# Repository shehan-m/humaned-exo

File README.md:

<p align="center">
  <a>
    
    <h1 align="center">HumanEd Exoskeleton Team</h1>
  </a>
</p>

<p align="center">

  Welcome to the HumanEd Exoskeleton Team Github repository! Check out the [project wiki](https://github.com/shehan-m/humaned-exo/wiki) for more information on the project.
</p>

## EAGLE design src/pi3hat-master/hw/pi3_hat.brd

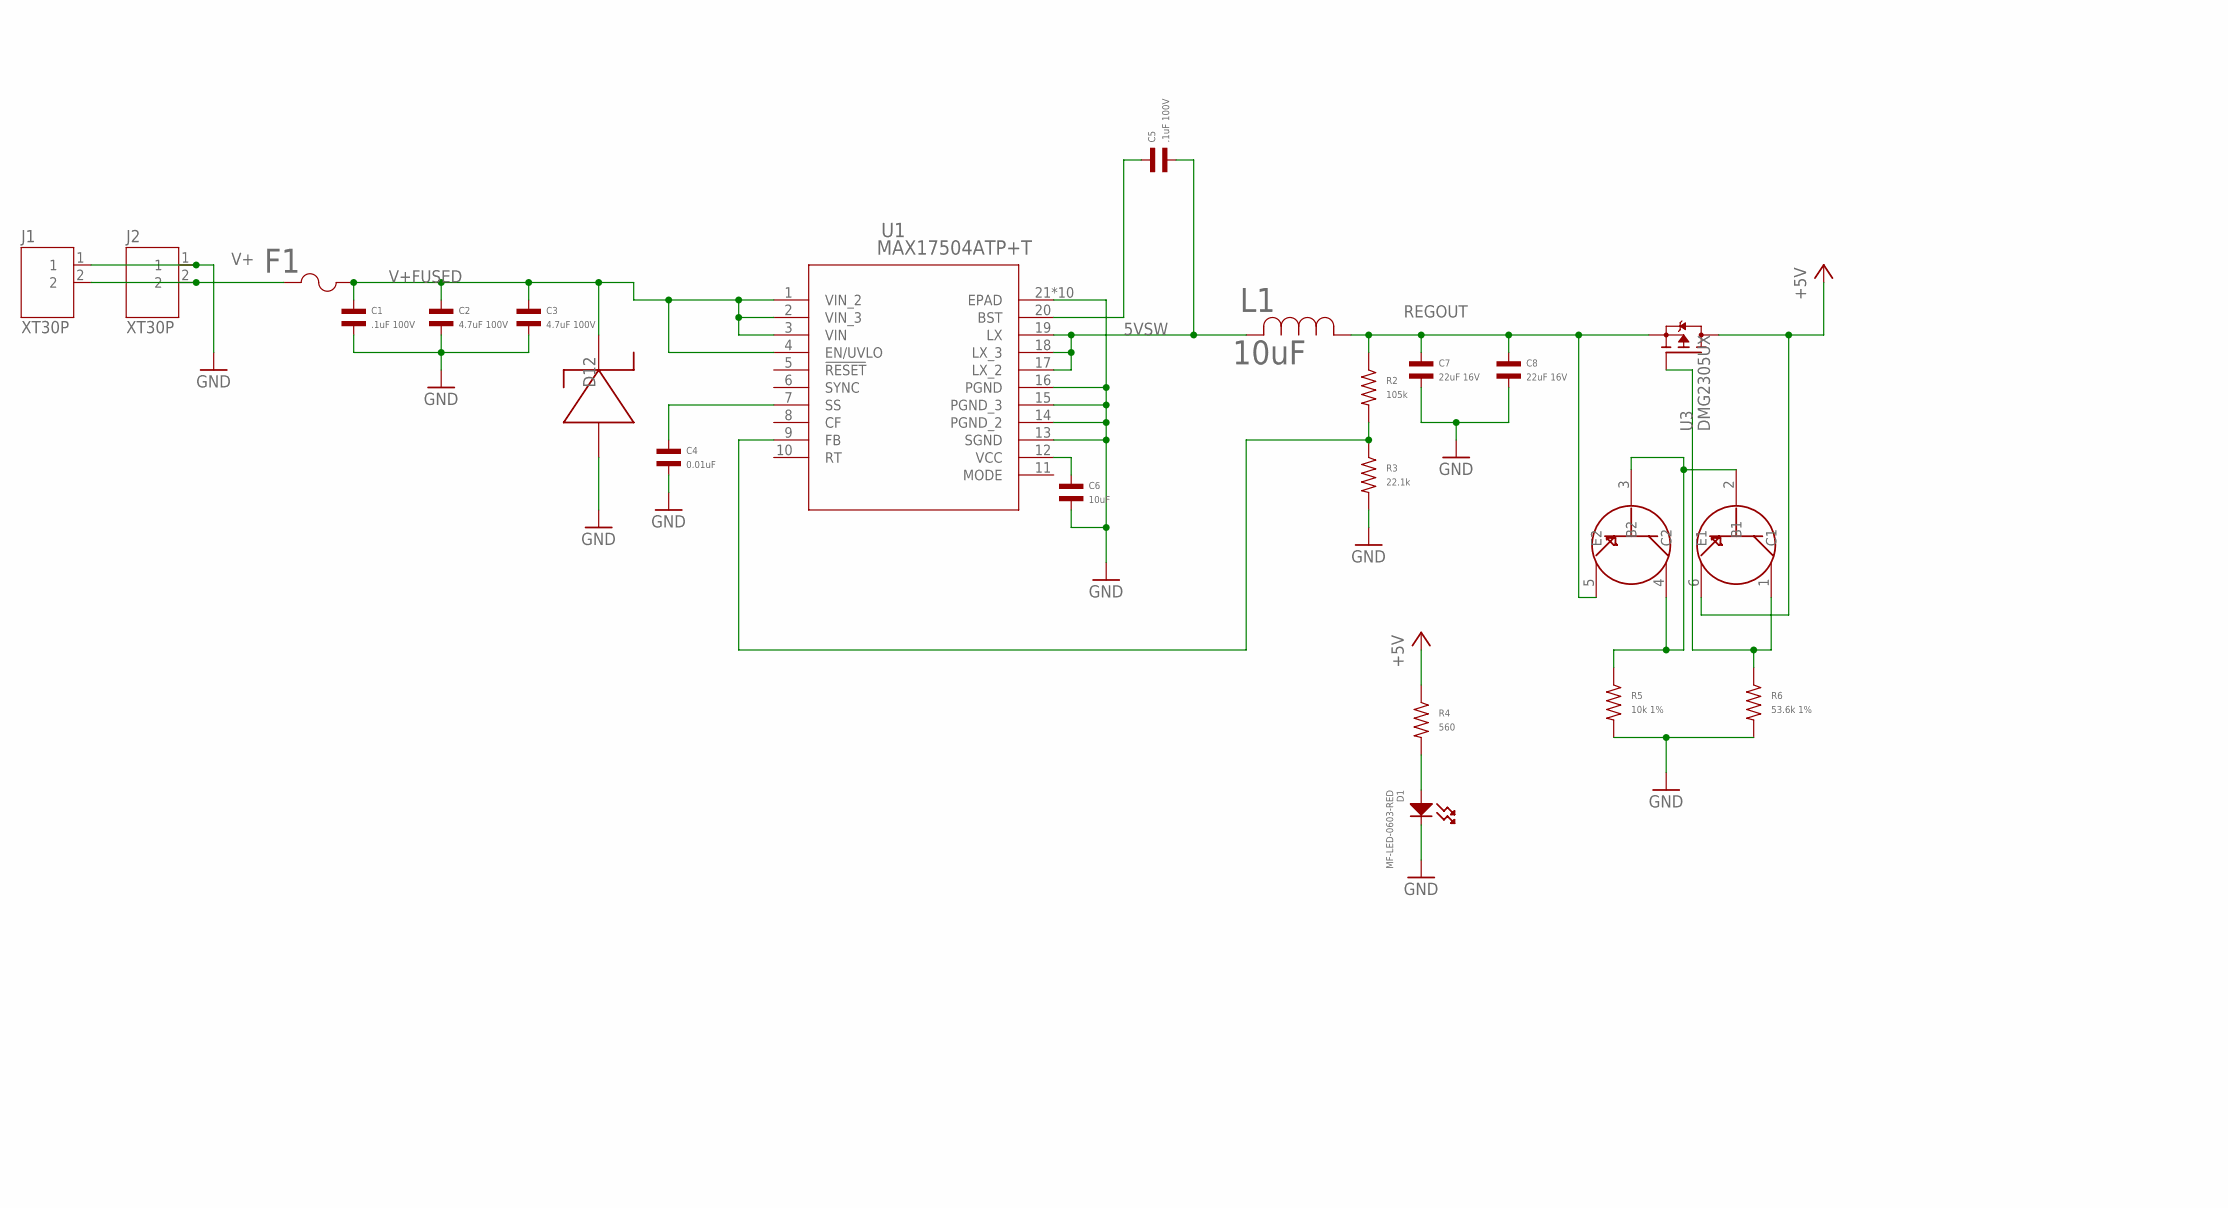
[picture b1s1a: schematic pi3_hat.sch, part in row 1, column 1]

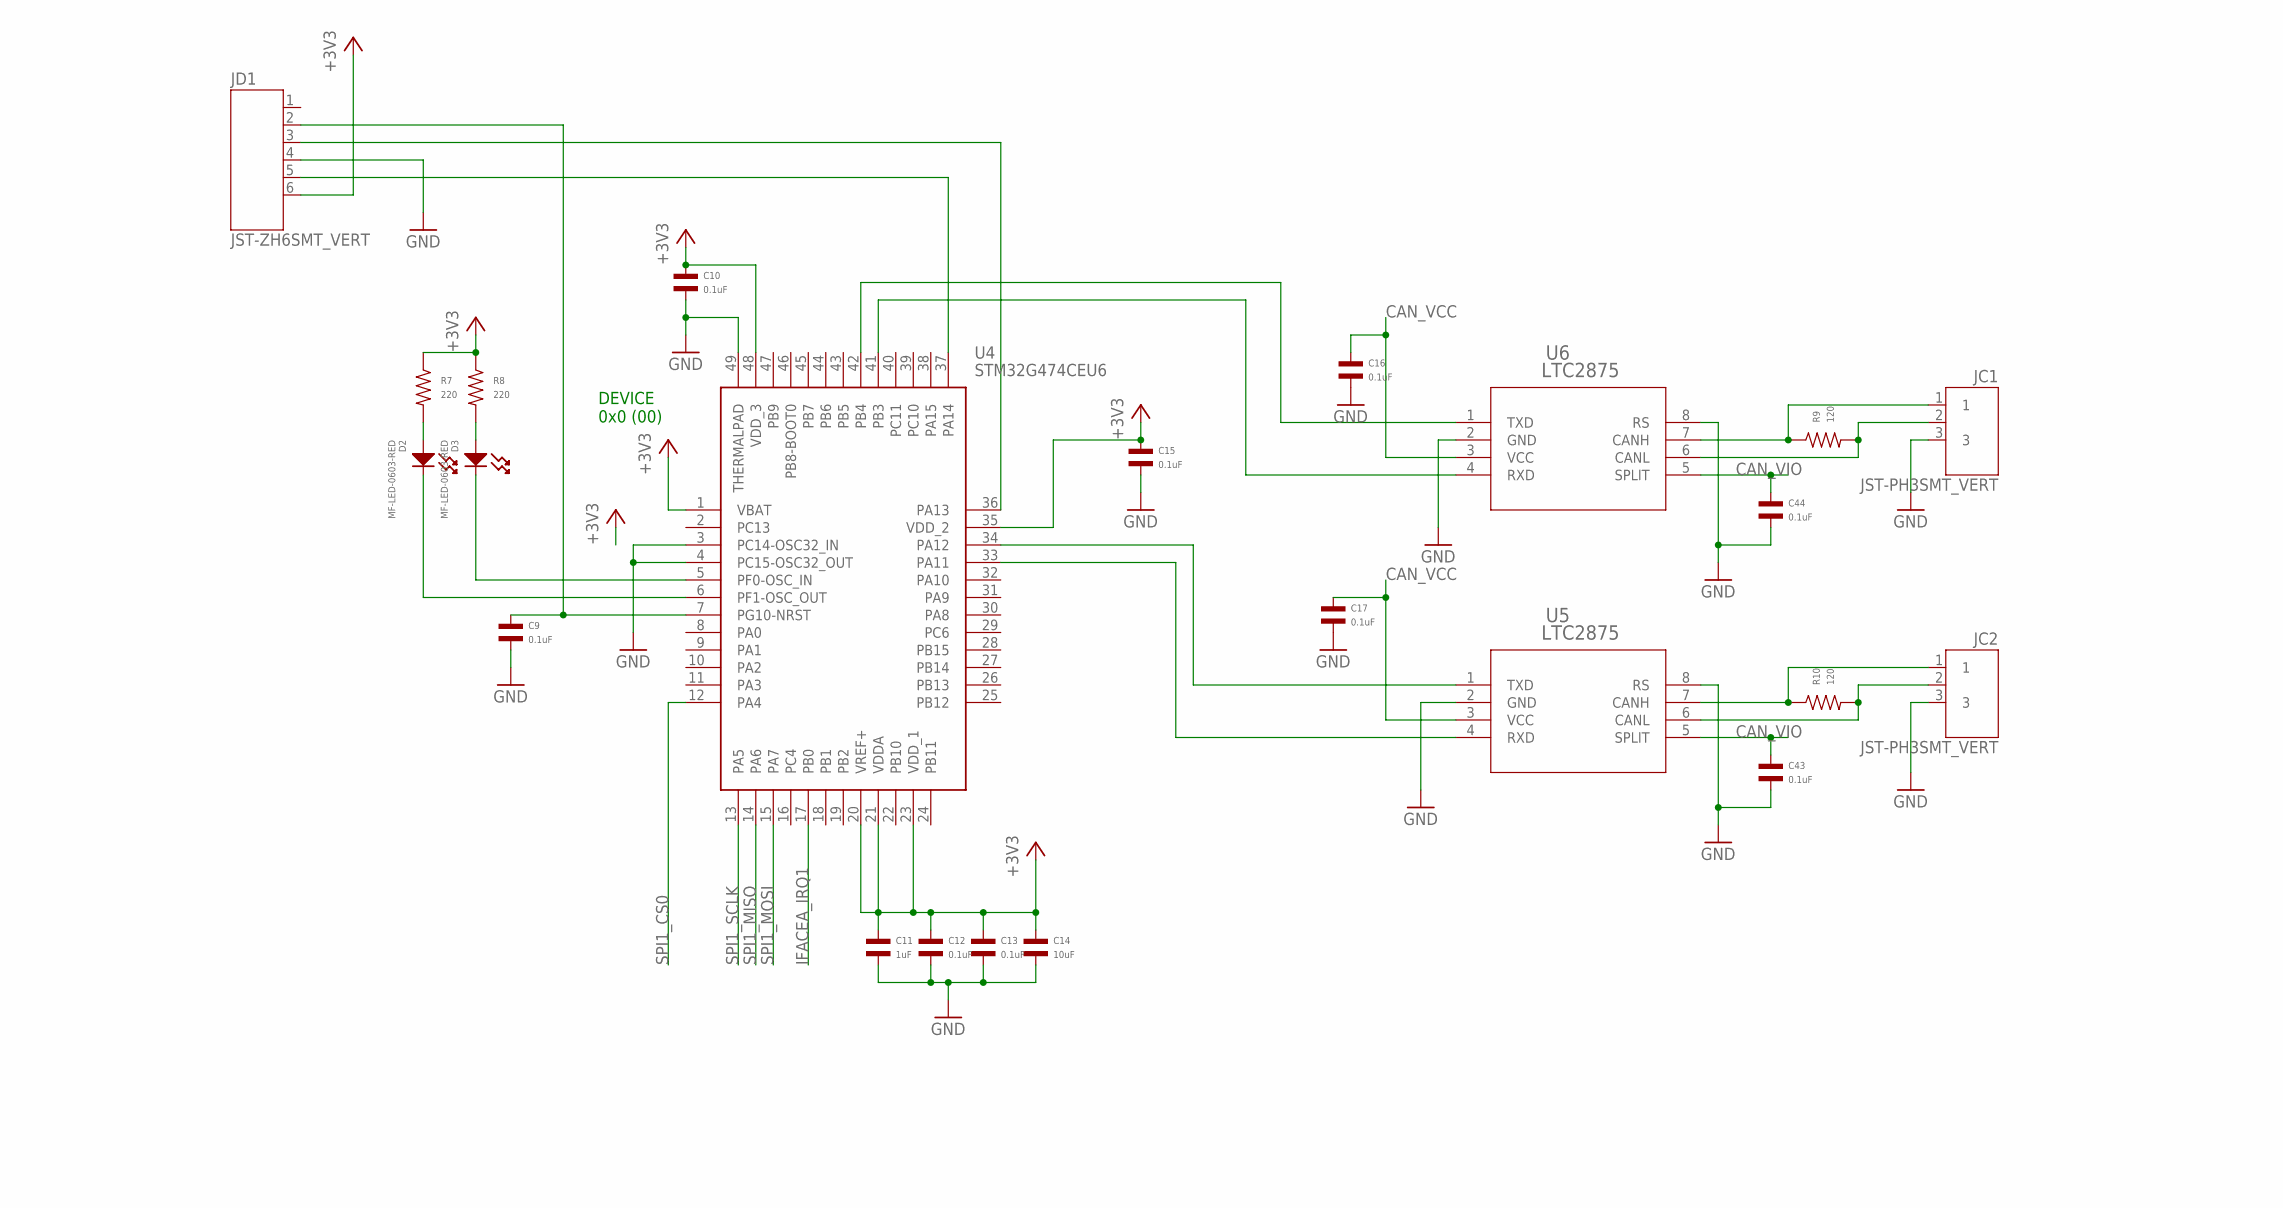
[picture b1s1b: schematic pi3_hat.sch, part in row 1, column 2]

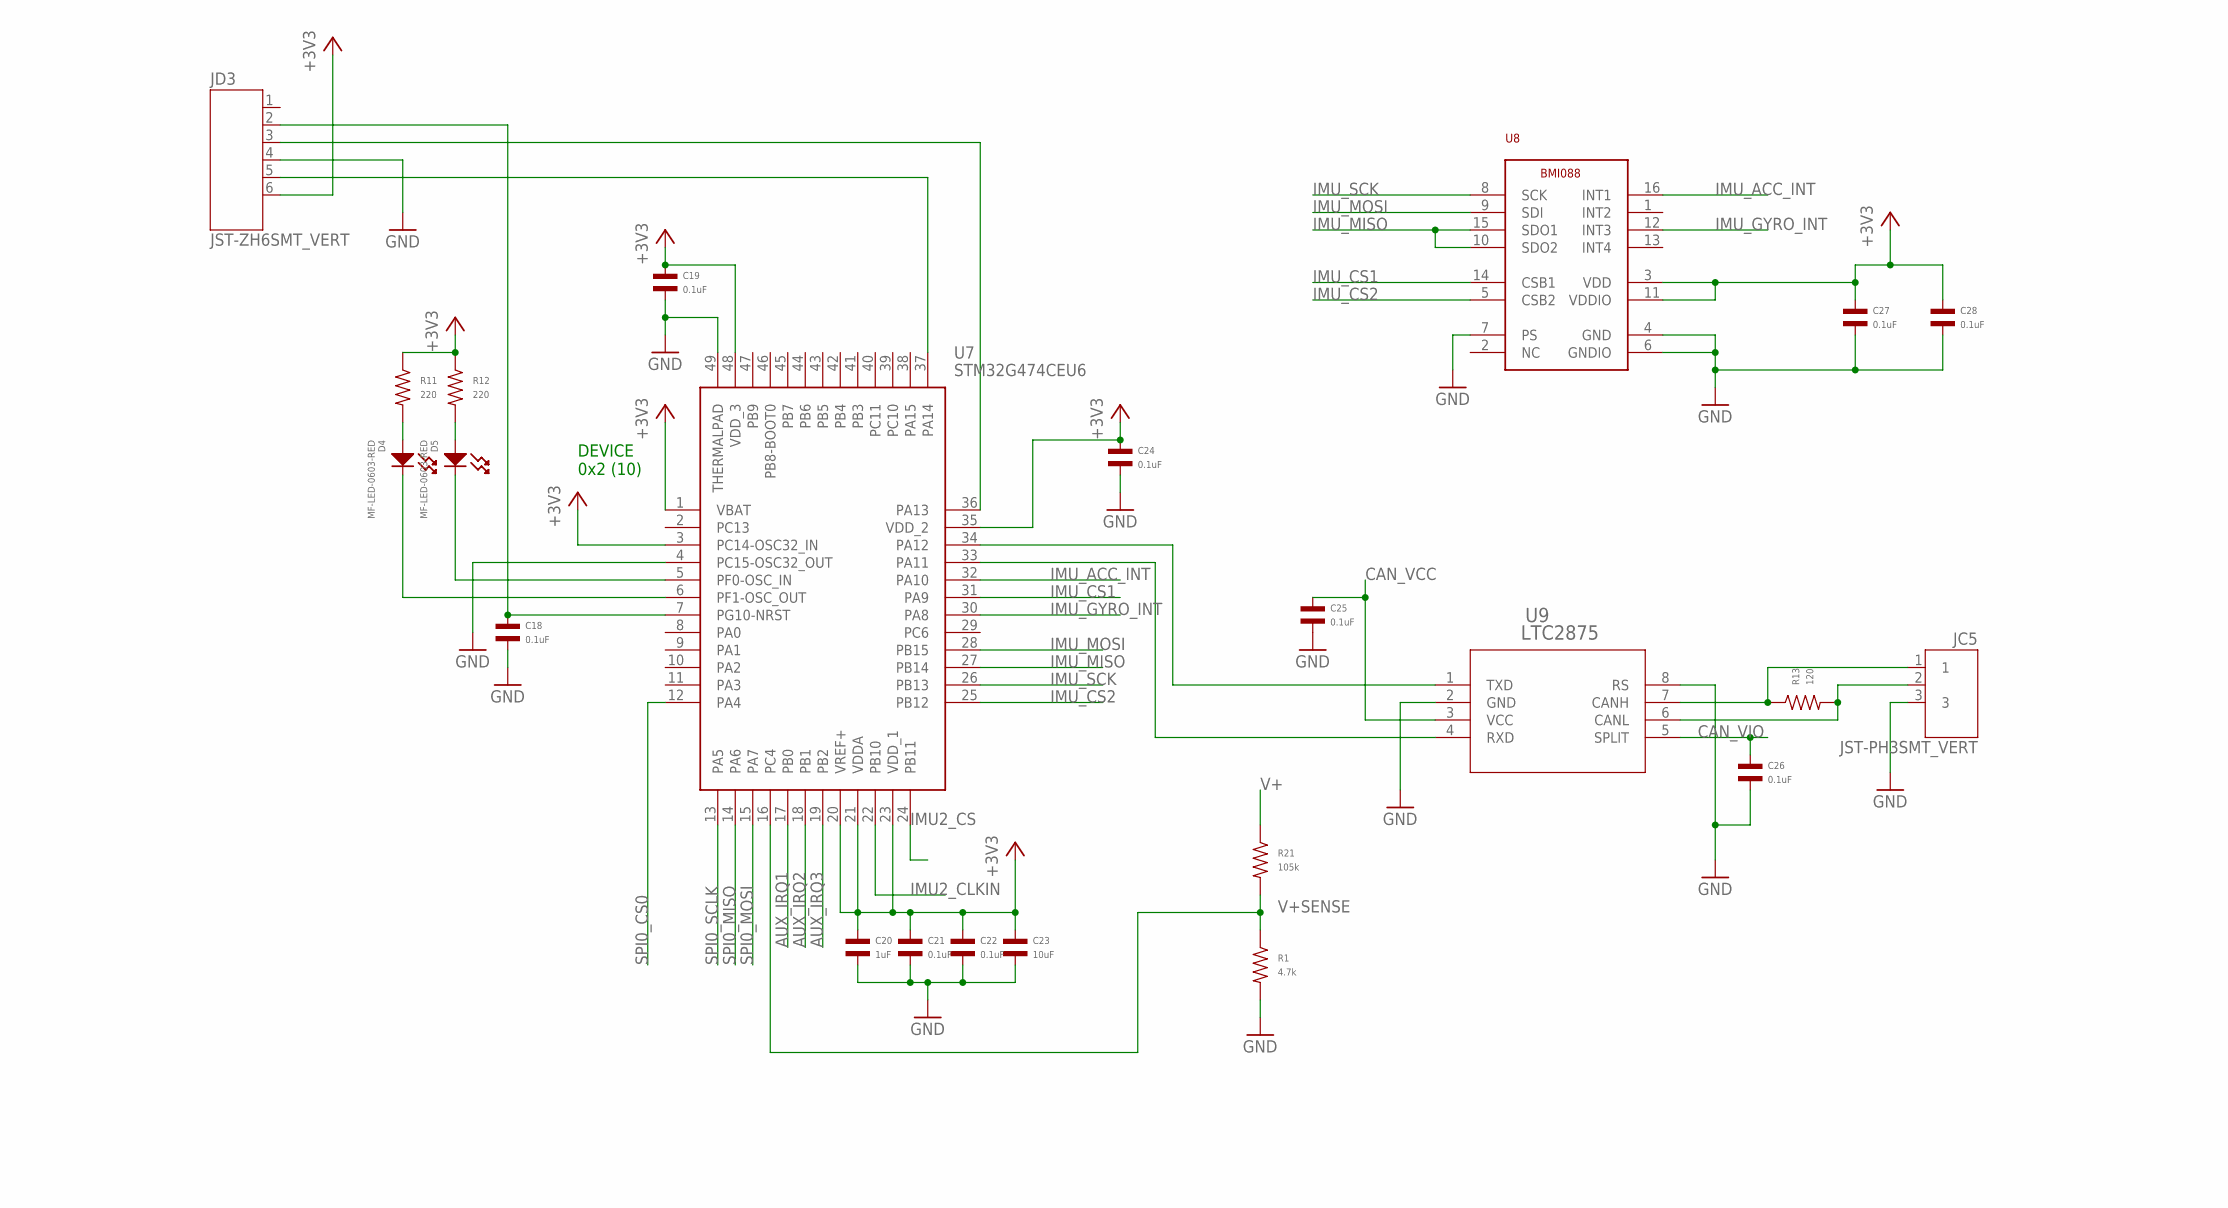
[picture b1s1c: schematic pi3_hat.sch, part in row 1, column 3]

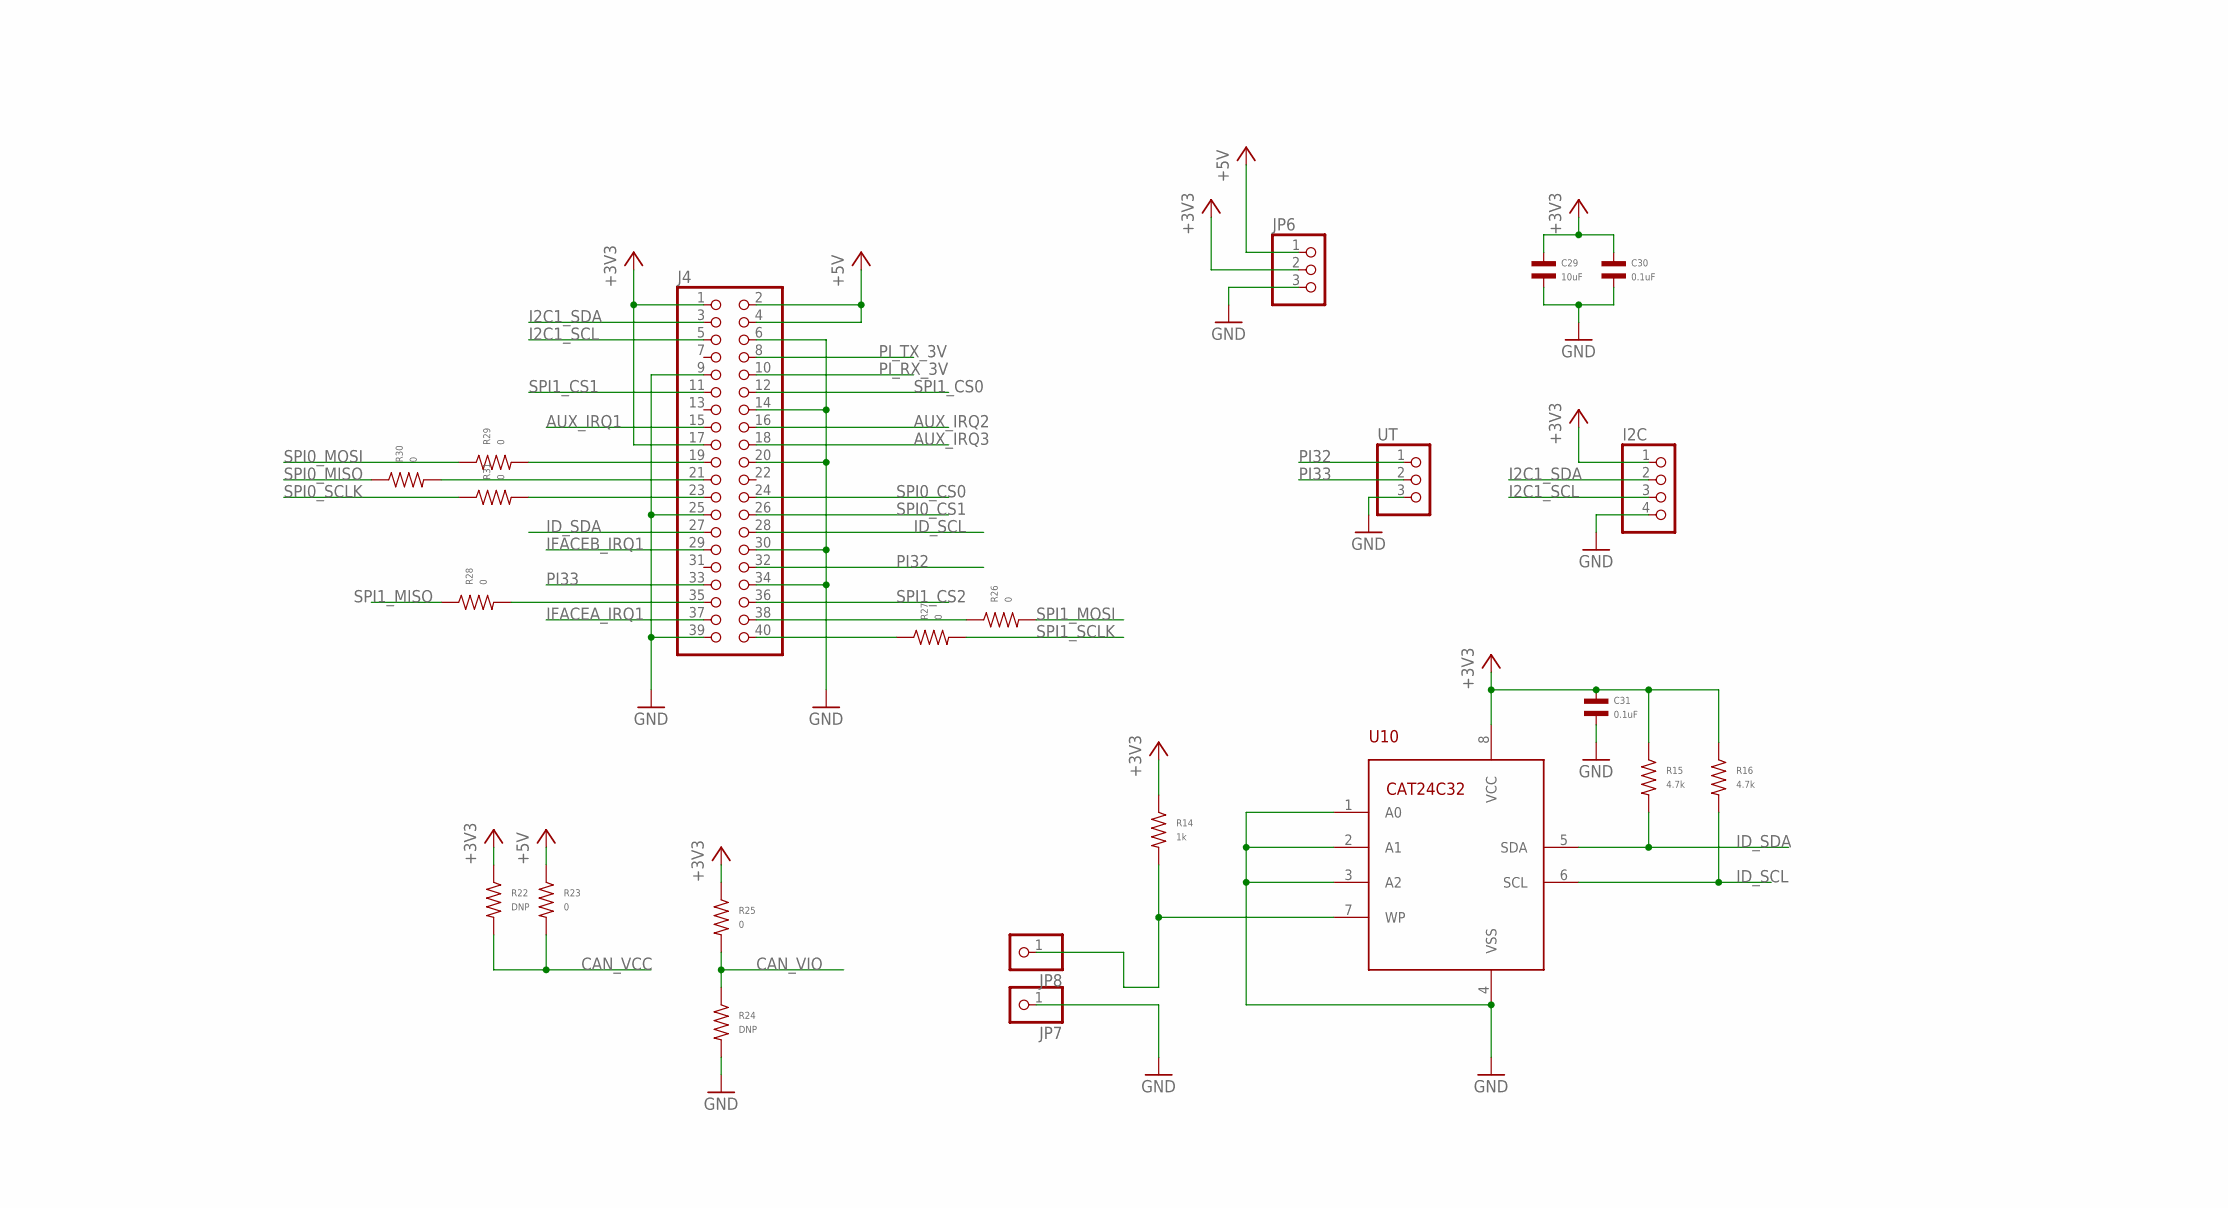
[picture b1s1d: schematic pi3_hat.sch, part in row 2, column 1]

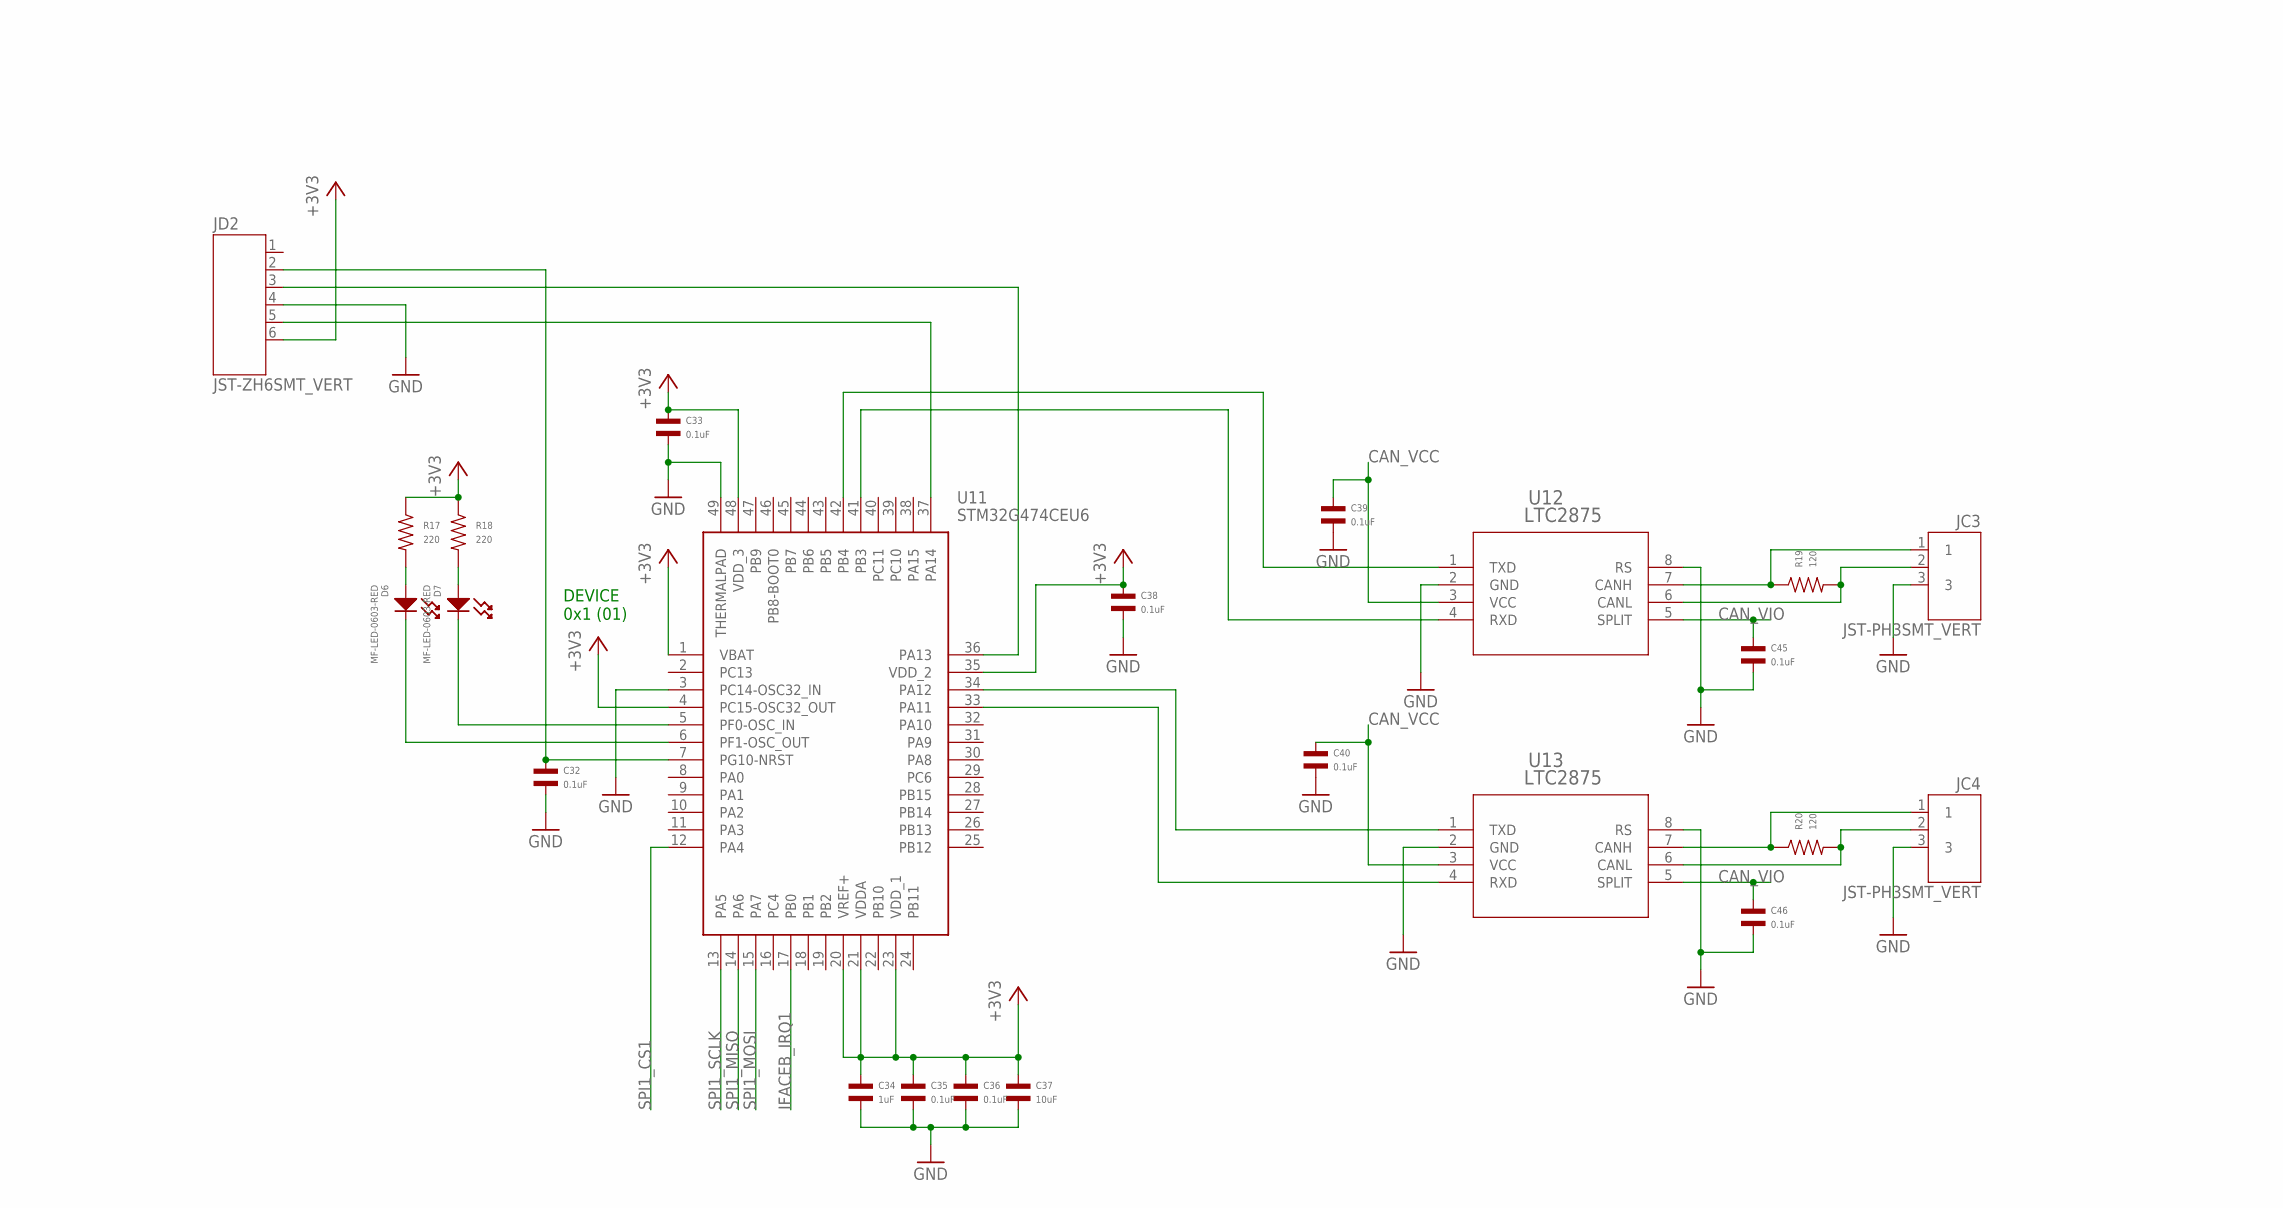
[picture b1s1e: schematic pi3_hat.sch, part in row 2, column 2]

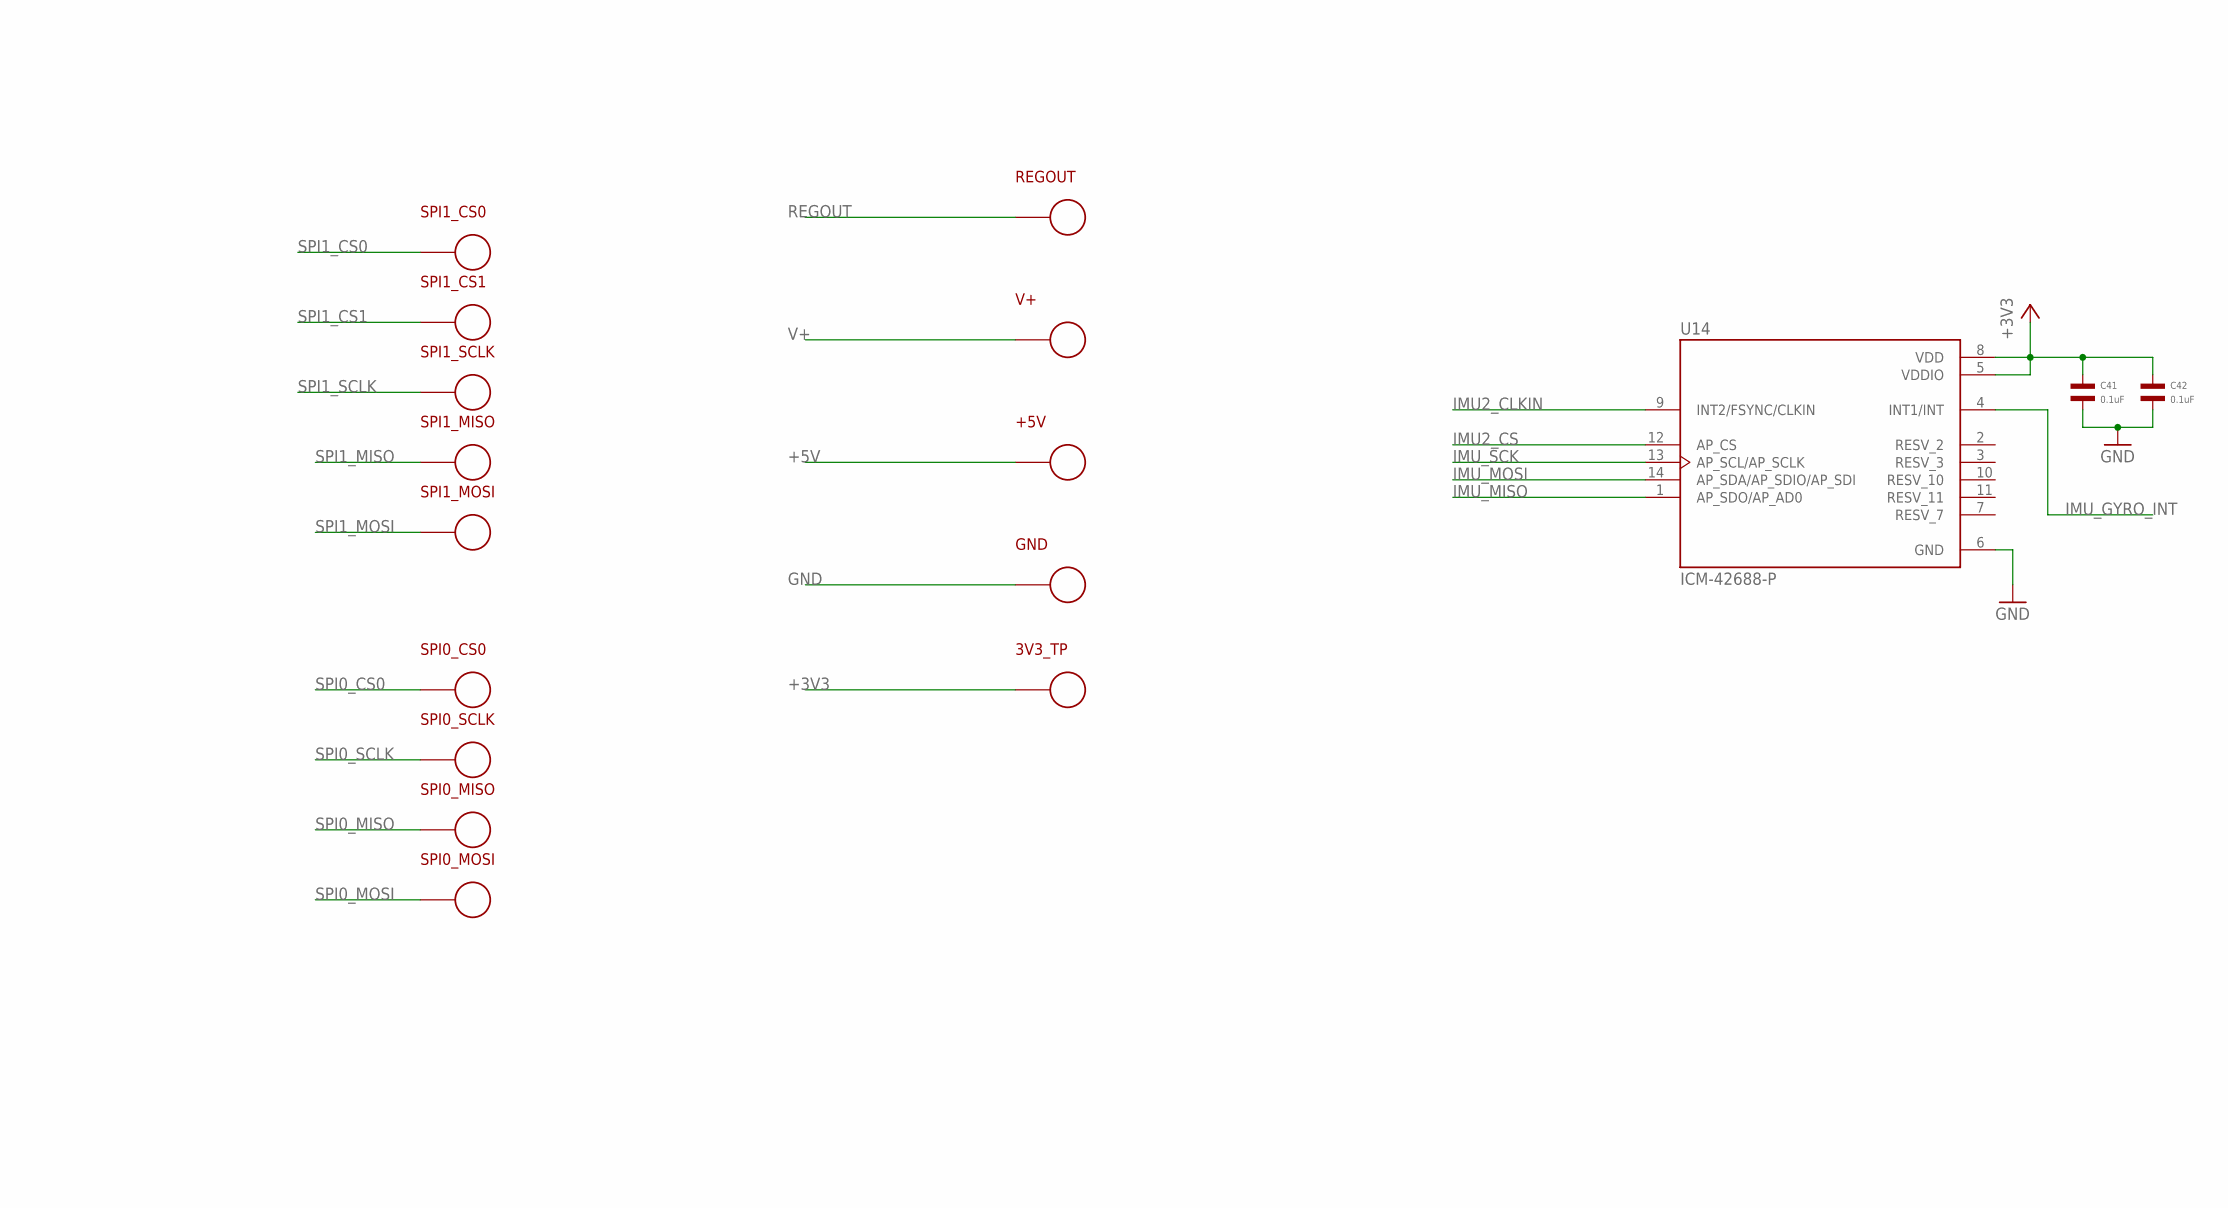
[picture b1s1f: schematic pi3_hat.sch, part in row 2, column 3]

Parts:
3V3_TP: PAD24AWG_PAD; 24AWG_PAD
+5V: PAD24AWG_PAD; 24AWG_PAD
C1, C5: .1uF 100V; C0805; MPN 08051C104KAZ2A
C2, C3: 4.7uF 100V; C1206; MPN GRJ31CC72A475KE01K
C4: 0.01uF; C0603; MPN MF-CAP-0603-0.01uF
C6, C14, C23, C29, C37: 10uF; C1206; MPN MF-CAP-1206-10uF
C7, C8: 22uF 16V; C1210; MPN CL32A226KOJNNNE
C9, C10, C12, C13, C15, C16, C17, C18, C19, C21, C22, C24, C25, C26, C27, C28, C30, C31, C32, C33, C35, C36, C38, C39, C40, C41, C42, C43, C44, C45, C46: 0.1uF; C0402; MPN MF-CAP-0402-0.1uF
C11, C20, C34: 1uF; C0402; MPN MF-CAP-0402-1uF
D1, D2, D4, D6: MF-LED-0603-RED; LED0603
D3, D5, D7: MF-LED-0603-RED; LED0603; MPN MF-LED-0603-GREEN
D12: SMF; MPN SMF51A
F1: MFU0603FF04000P100; FUS_VISHAY_MFU0603; MPN 0686F4000-01
GND: PAD24AWG_PAD; 24AWG_PAD
I2C: PINHD-1X4; 1X04; MPN MF-CON-2.54mm-01x04
J1, J2: XT30P; MPN XT30UPB-M
J4: PI3_HEADER2X20-FLIP; 2X20FLIP; MPN PPPC202LFBN-RC
JC1, JC2, JC3, JC4, JC5: JST-PH3SMT_VERT; JST_B3B_PH-SM4-TB(LF)(SN); MPN B3B-PH-SM4-TB(LF)(SN)
JD1, JD2, JD3: JST-ZH6SMT_VERT; JST_B6B-ZR-SM4-TF(LF)(SN); MPN B6B-ZR-SM4-TF(LF)(SN)
JP6: PINHD-1X3; 1X03; MPN MF-CON-2.54mm-01x03
JP7, JP8: PINHD-1X1; 1X01
L1: 10uF; IND_YUDEN_NS10165_YDN; MPN NS10165T100MNA
R1, R15, R16: 4.7k; R0402; MPN MF-RES-0402-4.7K
R2, R21: 105k; R0402; MPN RC0402FR-07105KL
R3: 22.1k; R0402; MPN RC0402FR-0722K1L
R4: 560; R0402; MPN MF-RES-0402-560
R5: 10k 1%; R0603; MPN RC0603FR-0710KL
R6: 53.6k 1%; R0603; MPN RC0603FR-0753K6L
R7, R8, R11, R12, R17, R18: 220; R0402; MPN MF-RES-0402-220
R9, R10, R13, R19, R20: 120; R0402; MPN RC0402FR-07120RL
R14: 1k; R0402; MPN MF-RES-0402-1K
R22, R24: DNP; R0402; MPN MF-RES-0402-0
R23, R25, R26, R27, R28, R29, R30, R31: 0; R0402; MPN MF-RES-0402-0
REGOUT: PAD24AWG_PAD; 24AWG_PAD
SPI0_CS0, SPI0_MISO, SPI0_MOSI, SPI0_SCLK, SPI1_CS0, SPI1_CS1, SPI1_MISO, SPI1_MOSI, SPI1_SCLK: PAD24AWG_PAD; 24AWG_PAD
U1: MAX17504ATP+T; 21-0140L_T2055-4_MXM; MPN MAX17504ATP+T
U2: DMMT5401; SOT26; MPN DMMT5401-7-F
U3: DMG2305UX; SOT23; MPN AO3415A
U4, U7, U11: STM32G474CEU6; QFN50P700X700X60-49N; MPN STM32G474CEU6
U5, U6, U9, U12, U13: LTC2875; SOIC8; MPN TCAN1057AEVDRQ1
U8: BMI088LGA16; LGA16; MPN BMI088
U10: CAT24C32UDFN8; UDFN8_2X3_ONS; MPN CAT24C32HU4I-GT3
U14: ICM-42688-P; PQFN50P300X250X97-14N; MPN ICM-42688-P
UT: PINHD-1X3; 1X03; MPN MF-CON-2.54mm-01x03
V+: PAD24AWG_PAD; 24AWG_PAD

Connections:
5VSW: C5.P$2, L1.2, U1.17 (LX_2), U1.18 (LX_3), U1.19 (LX)
+3V3: 3V3_TP.P$1, C10.P$1, C11.P$1, C12.P$1, C13.P$1, C14.P$1, C15.P$1, C19.P$1, C20.P$1, C21.P$1, C22.P$1, C23.P$1, C24.P$1, C27.P$1, C28.P$1, C29.P$1, C30.P$1, C31.P$1, C33.P$1, C34.P$1, C35.P$1, C36.P$1, C37.P$1, C38.P$1, C41.P$1, C42.P$1, I2C.1, J4.1, J4.17, JD1.6, JD2.6, JD3.6, JP6.2, R7.P$1, R8.P$1, R11.P$1, R12.P$1, R14.P$1, R15.P$1, R16.P$1, R17.P$1, R18.P$1, R22.P$1, R25.P$1, U4.1 (VBAT), U4.20 (VREF+), U4.21 (VDDA), U4.23 (VDD_1), U4.35 (VDD_2), U4.48 (VDD_3), U7.1 (VBAT), U7.3 (PC14-OSC32_IN), U7.20 (VREF+), U7.21 (VDDA), U7.23 (VDD_1), U7.35 (VDD_2), U7.48 (VDD_3), U8.3 (VDD), U8.11 (VDDIO), U10.8 (VCC), U11.1 (VBAT), U11.4 (PC15-OSC32_OUT), U11.20 (VREF+), U11.21 (VDDA), U11.23 (VDD_1), U11.35 (VDD_2), U11.48 (VDD_3), U14.5 (VDDIO), U14.8 (VDD)
+5V: +5V.P$1, J4.2, J4.4, JP6.1, R4.P$1, R23.P$1, U2.6 (E1), U3.3 (D)
AUX_IRQ1: J4.15, U7.17 (PB0)
AUX_IRQ2: J4.16, U7.18 (PB1)
AUX_IRQ3: J4.18, U7.19 (PB2)
CAN_VCC: C16.P$1, C17.P$1, C25.P$1, C39.P$1, C40.P$1, R22.P$2, R23.P$2, U5.3 (VCC), U6.3 (VCC), U9.3 (VCC), U12.3 (VCC), U13.3 (VCC)
CAN_VIO: C26.P$1, C43.P$1, C44.P$1, C45.P$1, C46.P$1, R24.P$1, R25.P$2, U5.5 (SPLIT), U6.5 (SPLIT), U9.5 (SPLIT), U12.5 (SPLIT), U13.5 (SPLIT)
FB: R2.P$2, R3.P$1, U1.9 (FB)
GND: C1.P$2, C2.P$2, C3.P$2, C4.P$2, C6.P$2, C7.P$2, C8.P$2, C9.P$2, C10.P$2, C11.P$2, C12.P$2, C13.P$2, C14.P$2, C15.P$2, C16.P$2, C17.P$2, C18.P$2, C19.P$2, C20.P$2, C21.P$2, C22.P$2, C23.P$2, C24.P$2, C25.P$2, C26.P$2, C27.P$2, C28.P$2, C29.P$2, C30.P$2, C31.P$2, C32.P$2, C33.P$2, C34.P$2, C35.P$2, C36.P$2, C37.P$2, C38.P$2, C39.P$2, C40.P$2, C41.P$2, C42.P$2, C43.P$2, C44.P$2, C45.P$2, C46.P$2, D1.CATHODE, D12.A, GND.P$1, I2C.4, J1.1, J2.1, J4.6, J4.9, J4.14, J4.20, J4.25, J4.30, J4.34, J4.39, JC1.3, JC2.3, JC3.3, JC4.3, JC5.3, JD1.4, JD2.4, JD3.4, JP6.3, JP7.1, R1.P$2, R3.P$2, R5.P$2, R6.P$2, R24.P$2, U1.13 (SGND), U1.14 (PGND_2), U1.15 (PGND_3), U1.16 (PGND), U1.21 (EPAD), U1.22 (EPAD), U1.23 (EPAD), U1.24 (EPAD), U1.25 (EPAD), U1.26 (EPAD), U1.27 (EPAD), U1.28 (EPAD), U1.29 (EPAD), U1.30 (EPAD), U4.3 (PC14-OSC32_IN), U4.4 (PC15-OSC32_OUT), U4.49 (THERMALPAD), U5.2 (GND), U5.8 (RS), U6.2 (GND), U6.8 (RS), U7.4 (PC15-OSC32_OUT), U7.49 (THERMALPAD), U8.4 (GND), U8.6 (GNDIO), U8.7 (PS), U9.2 (GND), U9.8 (RS), U10.1 (A0), U10.2 (A1), U10.3 (A2), U10.4 (VSS), U11.3 (PC14-OSC32_IN), U11.49 (THERMALPAD), U12.2 (GND), U12.8 (RS), U13.2 (GND), U13.8 (RS), U14.6 (GND), UT.3
I2C1_SCL: I2C.3, J4.5
I2C1_SDA: I2C.2, J4.3
ID_SCL: J4.28, R16.P$2, U10.6 (SCL)
ID_SDA: J4.27, R15.P$2, U10.5 (SDA)
IFACEA_IRQ1: J4.37, U4.17 (PB0)
IFACEB_IRQ1: J4.29, U11.17 (PB0)
IMU2_CLKIN: U7.22 (PB10), U14.9 (INT2/FSYNC/CLKIN)
IMU2_CS: U7.24 (PB11), U14.12 (AP_CS)
IMU_ACC_INT: U7.32 (PA10), U8.16 (INT1)
IMU_CS1: U7.31 (PA9), U8.14 (CSB1)
IMU_CS2: U7.25 (PB12), U8.5 (CSB2)
IMU_GYRO_INT: U7.30 (PA8), U8.12 (INT3), U14.4 (INT1/INT)
IMU_MISO: U7.27 (PB14), U8.10 (SDO2), U8.15 (SDO1), U14.1 (AP_SDO/AP_AD0)
IMU_MOSI: U7.28 (PB15), U8.9 (SDI), U14.14 (AP_SDA/AP_SDIO/AP_SDI)
IMU_SCK: U7.26 (PB13), U8.8 (SCK), U14.13 (AP_SCL/AP_SCLK)
unnamed: R5.P$1, U2.2 (B1), U2.3 (B2), U2.4 (C2)
unnamed: JC1.1, R9.P$1, U6.7 (CANH)
unnamed: J4.38, R26.P$1
unnamed: JC1.2, R9.P$2, U6.6 (CANL)
unnamed: R6.P$1, U2.1 (C1), U3.1 (G)
unnamed: J4.40, R27.P$1
unnamed: JC2.1, R10.P$1, U5.7 (CANH)
unnamed: JC2.2, R10.P$2, U5.6 (CANL)
unnamed: D1.ANODE, R4.P$2
unnamed: J4.35, R28.P$2
unnamed: U4.33 (PA11), U5.4 (RXD)
unnamed: J4.19, R29.P$2
unnamed: C9.P$1, JD1.2, U4.7 (PG10-NRST)
unnamed: C5.P$1, U1.20 (BST)
unnamed: JD1.3, U4.36 (PA13)
unnamed: JD1.5, U4.37 (PA14)
unnamed: U4.41 (PB3), U6.4 (RXD)
unnamed: U4.42 (PB4), U6.1 (TXD)
unnamed: C4.P$1, U1.7 (SS)
unnamed: J4.21, R30.P$2
unnamed: C6.P$1, U1.12 (VCC)
unnamed: J4.23, R31.P$2
unnamed: JC3.1, R19.P$1, U12.7 (CANH)
unnamed: JC3.2, R19.P$2, U12.6 (CANL)
unnamed: JC4.1, R20.P$1, U13.7 (CANH)
unnamed: JC4.2, R20.P$2, U13.6 (CANL)
unnamed: D3.ANODE, R8.P$2
unnamed: D3.CATHODE, U4.5 (PF0-OSC_IN)
unnamed: D2.ANODE, R7.P$2
unnamed: D2.CATHODE, U4.6 (PF1-OSC_OUT)
unnamed: C32.P$1, JD2.2, U11.7 (PG10-NRST)
unnamed: JD2.3, U11.36 (PA13)
unnamed: JD2.5, U11.37 (PA14)
unnamed: D7.ANODE, R18.P$2
unnamed: D7.CATHODE, U11.5 (PF0-OSC_IN)
unnamed: D6.ANODE, R17.P$2
unnamed: D6.CATHODE, U11.6 (PF1-OSC_OUT)
unnamed: U11.33 (PA11), U13.4 (RXD)
unnamed: U11.34 (PA12), U13.1 (TXD)
unnamed: U11.41 (PB3), U12.4 (RXD)
unnamed: U11.42 (PB4), U12.1 (TXD)
unnamed: JP8.1, R14.P$2, U10.7 (WP)
unnamed: JC5.1, R13.P$1, U9.7 (CANH)
unnamed: JC5.2, R13.P$2, U9.6 (CANL)
unnamed: C18.P$1, JD3.2, U7.7 (PG10-NRST)
unnamed: JD3.3, U7.36 (PA13)
unnamed: JD3.5, U7.37 (PA14)
unnamed: D5.ANODE, R12.P$2
unnamed: D5.CATHODE, U7.5 (PF0-OSC_IN)
unnamed: D4.ANODE, R11.P$2
unnamed: D4.CATHODE, U7.6 (PF1-OSC_OUT)
unnamed: U7.33 (PA11), U9.4 (RXD)
unnamed: U7.34 (PA12), U9.1 (TXD)
unnamed: U4.34 (PA12), U5.1 (TXD)
PI32: J4.32, UT.1
PI33: J4.33, UT.2
PI_RX_3V: J4.10
PI_TX_3V: J4.8
REGOUT: C7.P$1, C8.P$1, L1.1, R2.P$1, REGOUT.P$1, U2.5 (E2), U3.2 (S)
SPI0_CS0: J4.24, SPI0_CS0.P$1, U7.12 (PA4)
SPI0_CS1: J4.26
SPI0_MISO: R30.P$1, SPI0_MISO.P$1, U7.14 (PA6)
SPI0_MOSI: R29.P$1, SPI0_MOSI.P$1, U7.15 (PA7)
SPI0_SCLK: R31.P$1, SPI0_SCLK.P$1, U7.13 (PA5)
SPI1_CS0: J4.12, SPI1_CS0.P$1, U4.12 (PA4)
SPI1_CS1: J4.11, SPI1_CS1.P$1, U11.12 (PA4)
SPI1_CS2: J4.36
SPI1_MISO: R28.P$1, SPI1_MISO.P$1, U4.14 (PA6), U11.14 (PA6)
SPI1_MOSI: R26.P$2, SPI1_MOSI.P$1, U4.15 (PA7), U11.15 (PA7)
SPI1_SCLK: R27.P$2, SPI1_SCLK.P$1, U4.13 (PA5), U11.13 (PA5)
V+: F1.1, J1.2, J2.2, R21.P$1, V+.P$1
V+FUSED: C1.P$1, C2.P$1, C3.P$1, D12.C, F1.2, U1.1 (VIN_2), U1.2 (VIN_3), U1.3 (VIN), U1.4 (EN/UVLO)
V+SENSE: R1.P$1, R21.P$2, U7.16 (PC4)

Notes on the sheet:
DEVICE 0x2 (10)
DEVICE 0x0 (00)
DEVICE 0x1 (01)

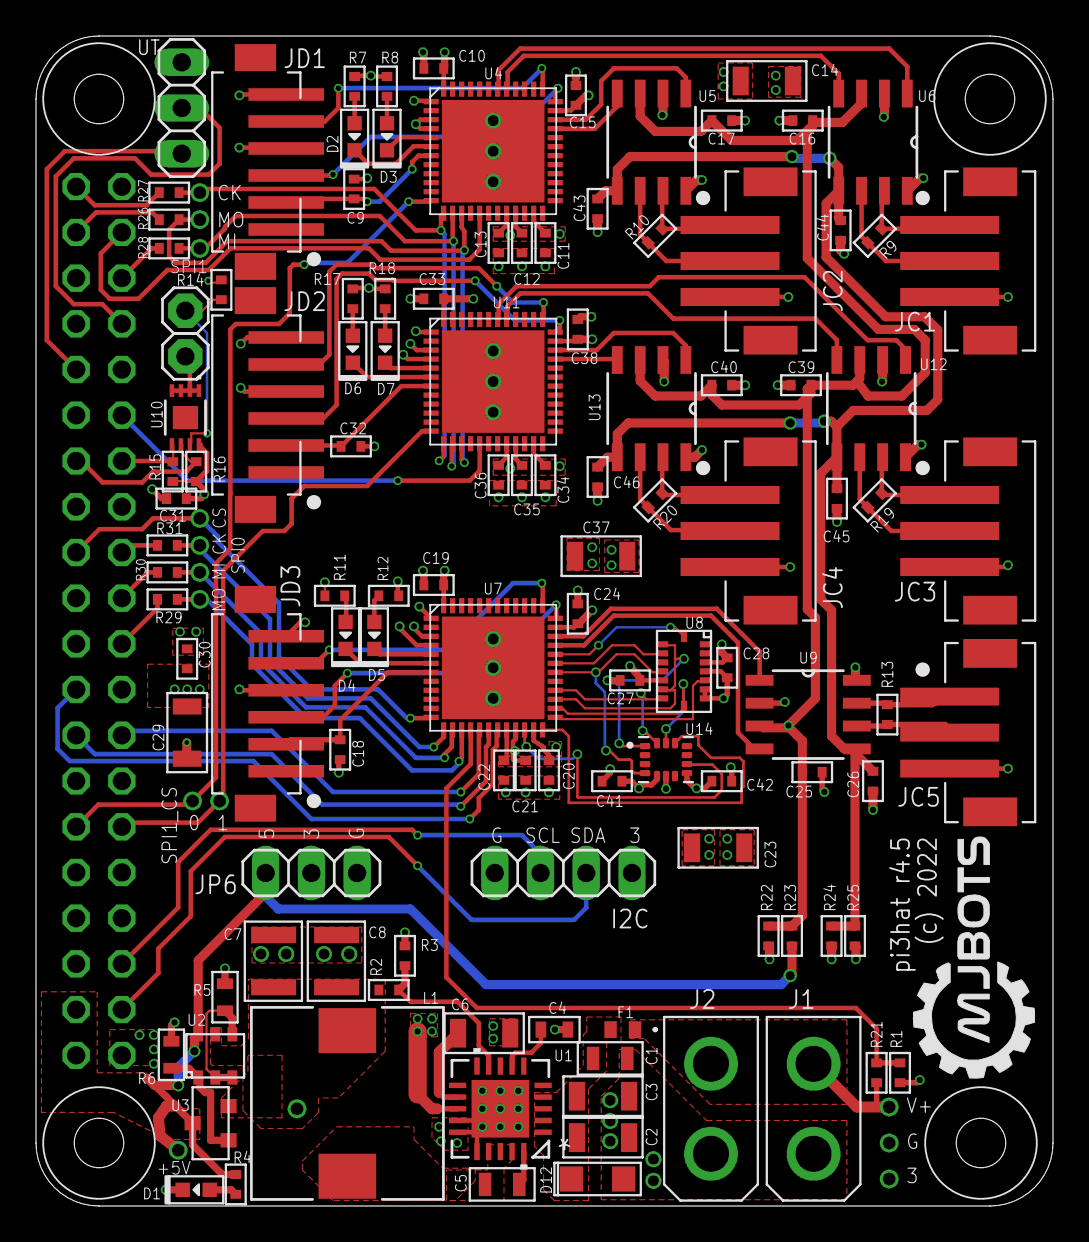
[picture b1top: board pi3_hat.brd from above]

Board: 4 copper layers, 56.5 x 65.0 mm, 131 parts (1 on the bottom side), 94 nets.

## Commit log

2024-10-03 Organising project
2024-11-07 Organising files
2024-11-07 Update main.py
    New gravity compensation implementation that does not use Drake. Since, the current design is essentially a 2 DoF pendulum, the inverse dynamics equation is available online so just using that. No ne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
2024-11-09 Added error handling
2024-11-12 added Pinocchio for dynamics calc
2024-11-13 more testing + using urdf for model
2024-11-13 added conversion to radians
2024-11-14 FIXED (hopefully)
    URDF file has a base link. Also, defined gravity in compensation code.
2024-11-14 Changed URDF + prep for testing
2024-11-14 Added pinocchio testing code
2024-11-18 IT WORKS!!!!
2024-12-23 Added some optimisations
    - Caching URDF file during initialisation
    - Added logging (replaced printing messages)
    + some more
2025-02-18 Improved efficiency (maybe)
2025-02-19 Organising...
2025-02-19 Correcting name

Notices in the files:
src/pi3hat-master/hw/pi3_hat.brd:
(c) 2022
src/pi3hat-master/hw/pi3_hat.sch:
(c) 2022 mjbots Robotic Systems
Licensed under the Apache 2.0 License
parts and their libraries:
COPYRIGHT: Copyright (C) 2018 Accelerated Designs. All rights reserved
